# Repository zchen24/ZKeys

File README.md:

## ZKeys
Custom USB keyboard (6-keys). The keyboard uses a Teensy LC microcontroller and 6 Cheery MX keys. 
I have programmed the keys to be media keys. 

| Previous | Play/Pause | Next    |
|----------|------------|---------|
| Mute     | Volume-    | Volume+ |

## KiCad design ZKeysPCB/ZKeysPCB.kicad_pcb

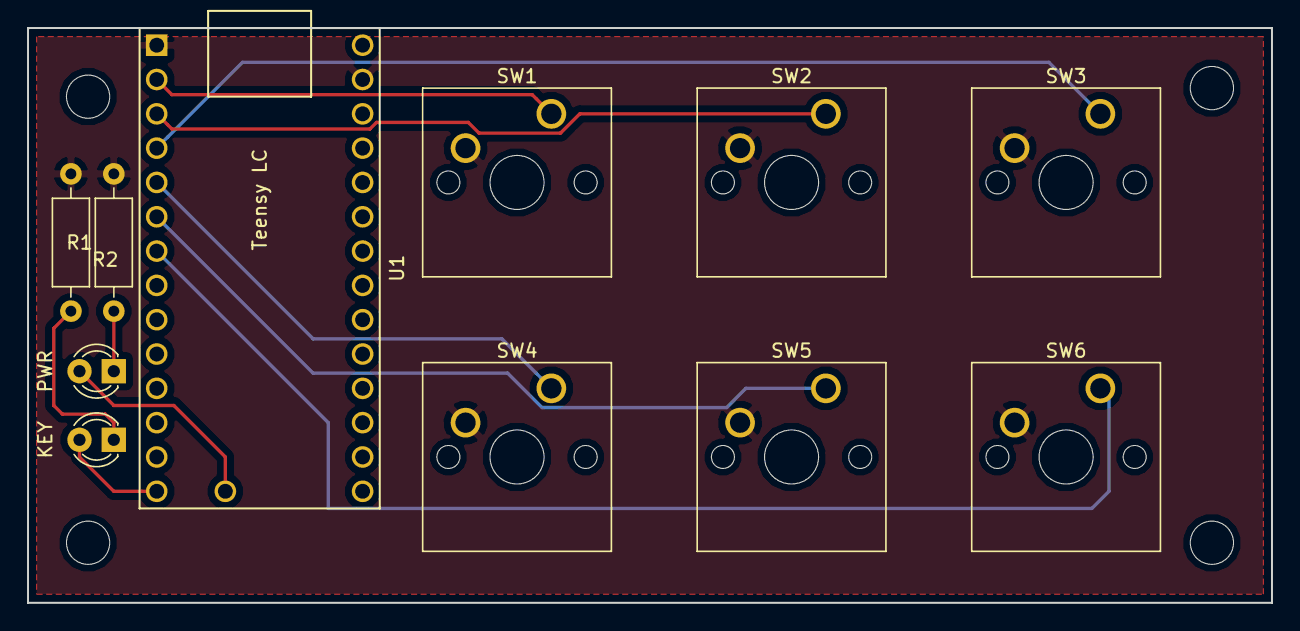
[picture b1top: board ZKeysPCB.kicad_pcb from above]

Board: 2 copper layers, 92.1 x 42.5 mm, 11 parts (0 on the bottom side), 11 nets.

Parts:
KEY: LED; LED_D3.0mm
PWR: LED; LED_D3.0mm
R1, R2: R; R_Axial_DIN0207_L6.3mm_D2.5mm_P10.16mm_Horizontal
SW1, SW2, SW3, SW4, SW5, SW6: SW_Push; SW_Cherry_MX1A_1.00u_PCB
U1: Teensy-LC; Teensy30_31_32_LC

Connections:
BTN_DEC: SW5.1, U1.6
BTN_INC: SW6.1, U1.7
BTN_MUTE: SW4.1, U1.5
BTN_NEXT: SW3.1, U1.4
BTN_PLAY: SW2.1, U1.3
BTN_PREV: SW1.1, U1.2
GND: R1.2, R2.2, SW1.2, SW2.2, SW3.2, SW4.2, SW5.2, SW6.2, U1.1, U1.32
unnamed: PWR.1, R1.1
unnamed: PWR.2, U1.16
unnamed: KEY.1, R2.1
unnamed: KEY.2, U1.14

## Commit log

2019-03-11 Added initial firmware and PCB
2019-03-11 updated PCB drawing
2019-03-11 Added icon pretty file
2019-03-11 Added README file
2019-04-01 Refactored Teensy firmware to allow media key toggle
2019-04-10 Added ZKeys Case v0.1
2019-04-10 Added Keycap part files
2019-04-20 Updated Zkeystop case
2019-04-20 Added Base arduino example
